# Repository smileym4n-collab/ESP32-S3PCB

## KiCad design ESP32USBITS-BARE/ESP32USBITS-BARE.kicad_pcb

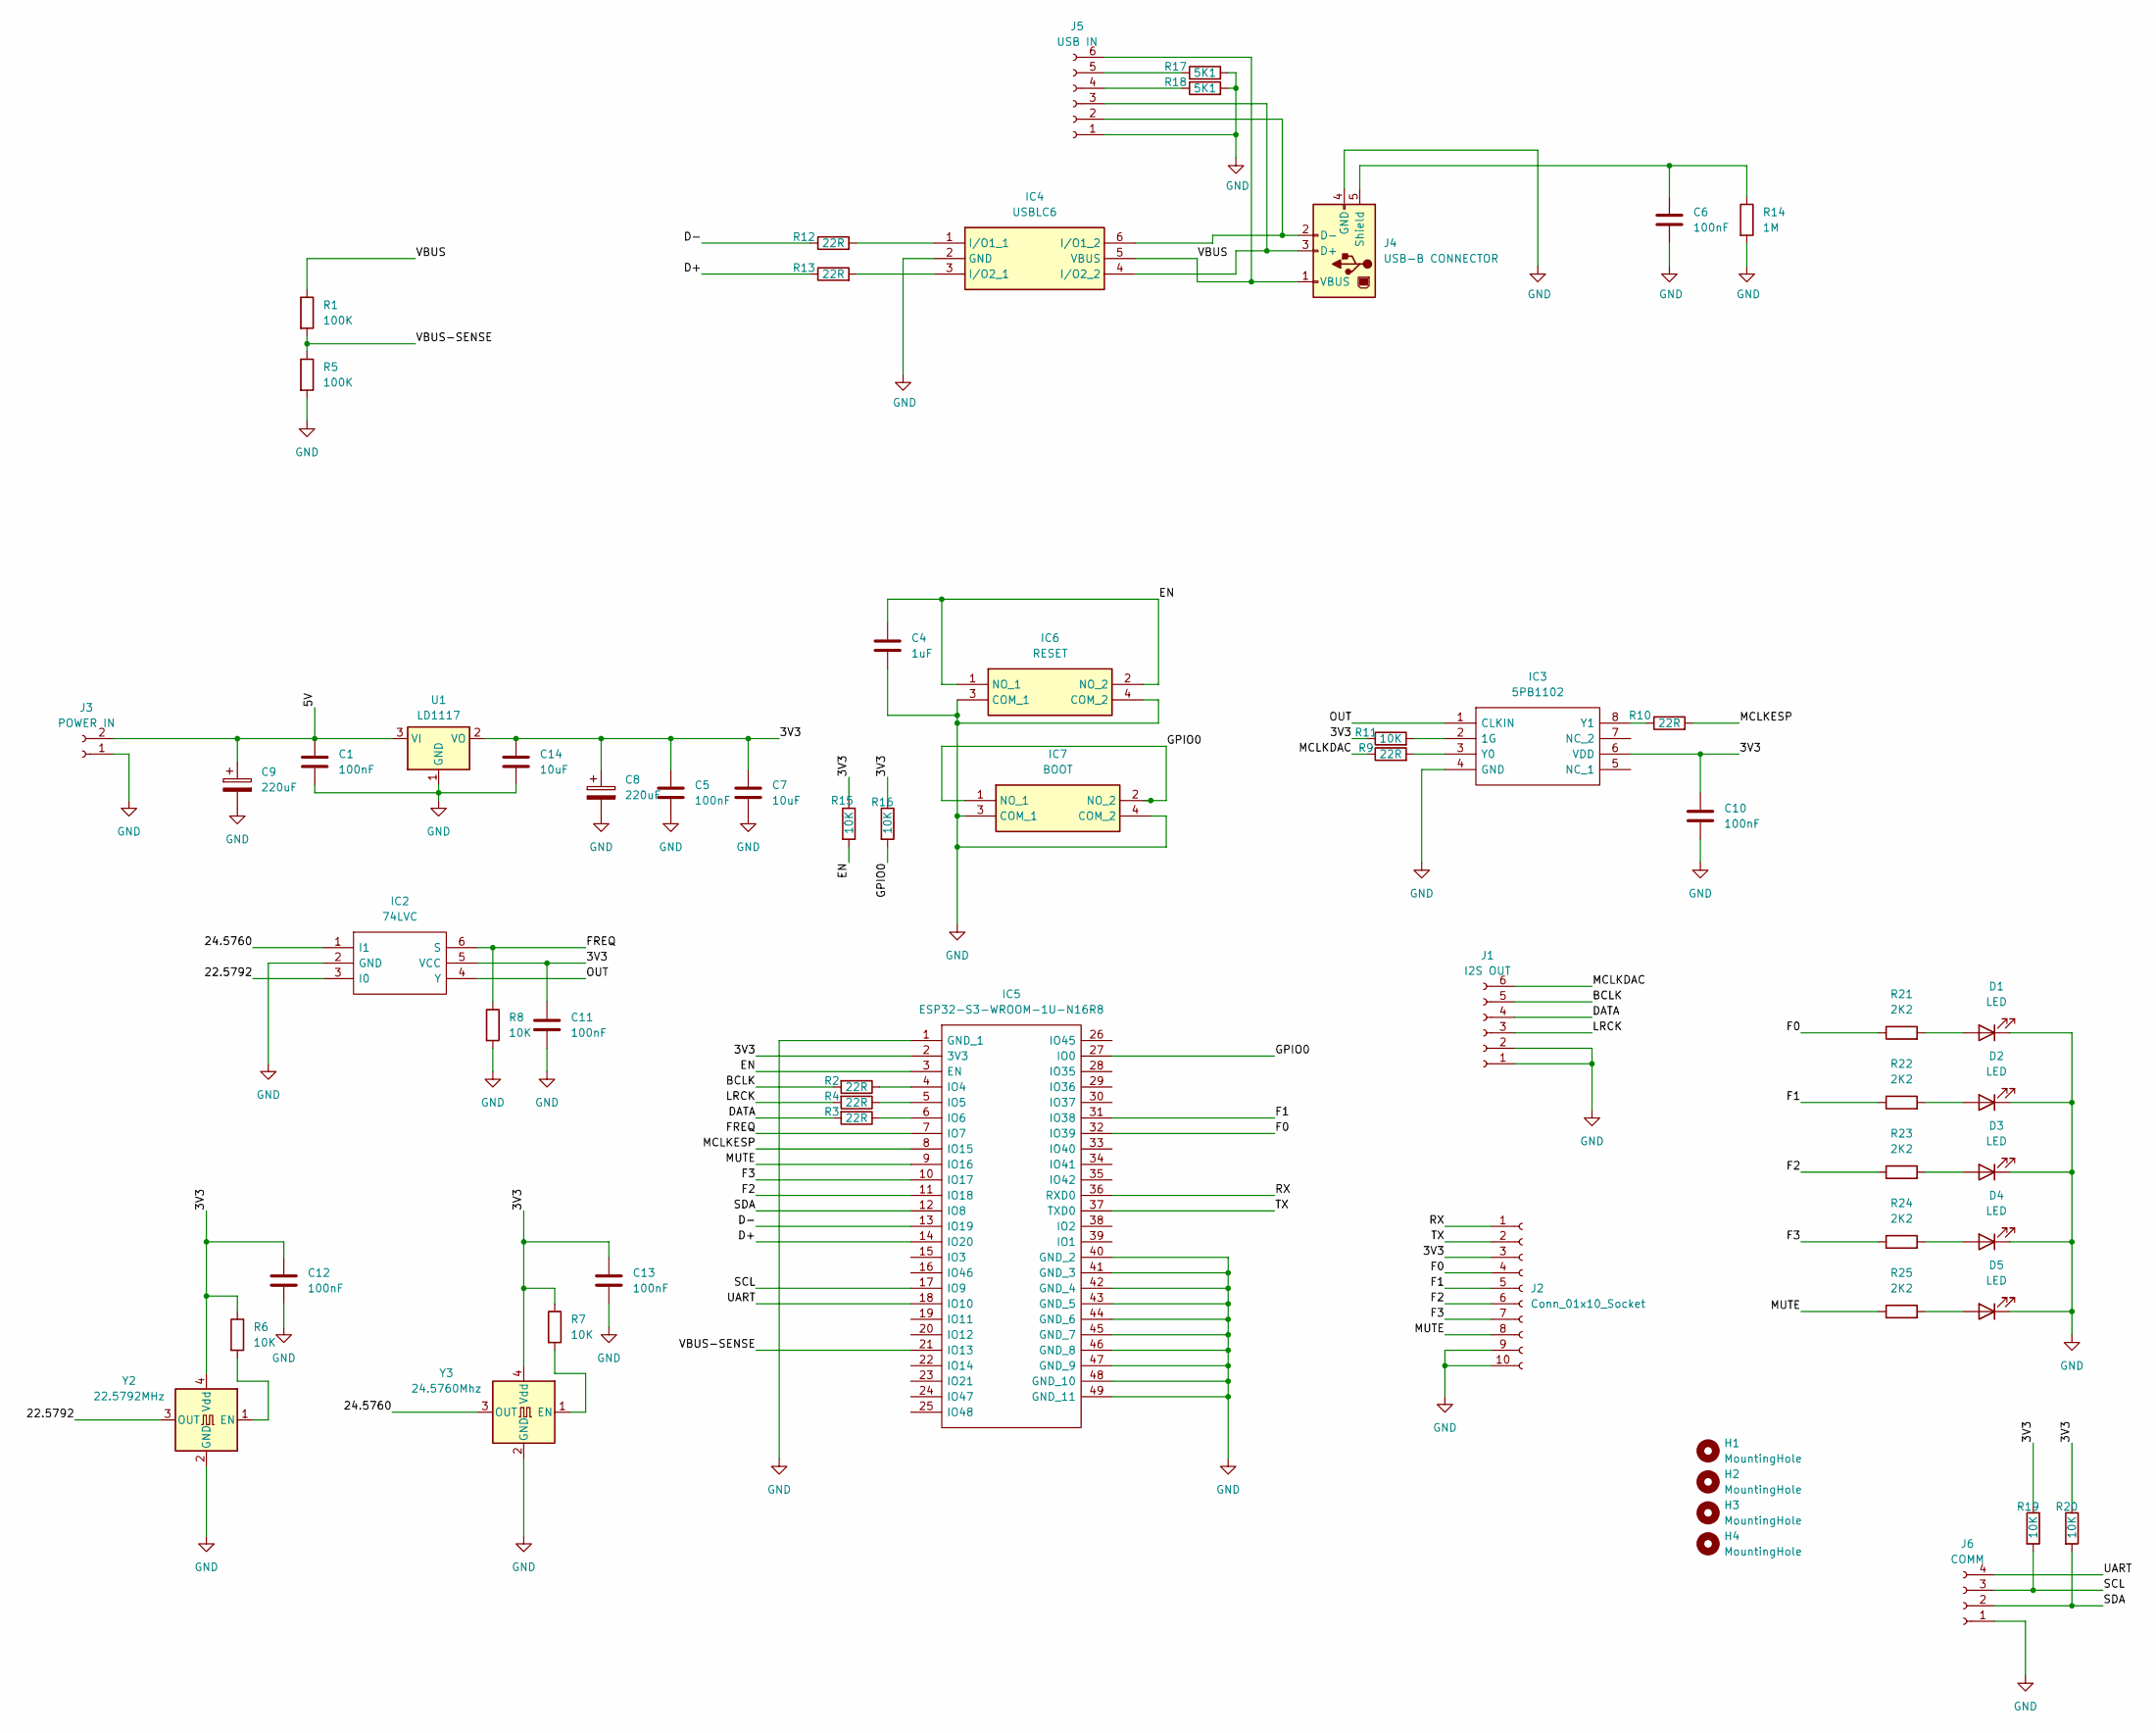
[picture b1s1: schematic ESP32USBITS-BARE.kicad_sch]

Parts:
C1, C5, C6, C10, C11, C12, C13: 100nF; C_1206_3216Metric_Pad1.33x1.80mm_HandSolder
C4: 1uF; C_1206_3216Metric_Pad1.33x1.80mm_HandSolder
C7: 10uF; C_1206_3216Metric_Pad1.33x1.80mm_HandSolder
C8, C9: 220uF; CP_Radial_D6.3mm_P2.50mm
C14: 10uF; C_0805_2012Metric_Pad1.18x1.45mm_HandSolder
D1, D2, D3, D4, D5: LED; LED_0805_2012Metric_Pad1.15x1.40mm_HandSolder
H1, H2, H3, H4: MountingHole; MountingHole_4mm
IC2: 74LVC; 74CBTLV3257PW; Manufacturer_Part_Number 74LVC1G157GW,125
IC3: 5PB1102; 5PB1102PGGK; Manufacturer_Part_Number 5PB1102PGGK
IC4: USBLC6; SOT-23-6_Handsoldering; Mouser Part Number 511-USBLC6-2SC6
IC5: ESP32-S3-WROOM-1U-N16R8; ESP32S3WROOM1UN16R8; Mouser Part Number 356-ESP32S3WM1UN16R8
IC6: RESET; TS026650BK100SCRD; Mouser Part Number 179-TS026650BK100SCR
IC7: BOOT; TS026650BK100SCRD; Mouser Part Number 179-TS026650BK100SCR
J1: I2S OUT; JST_XH_B6B-XH-A_1x06_P2.50mm_Vertical
J2: Conn_01x10_Socket; PinHeader_1x10_P2.54mm_Vertical
J3: POWER IN; JST_XH_B2B-XH-A_1x02_P2.50mm_Vertical
J4: USB-B CONNECTOR; USBC
J5: USB IN; JST_XH_B6B-XH-A_1x06_P2.50mm_Vertical
J6: COMM; PinHeader_1x04_P2.54mm_Vertical
R1, R5: 100K; R_0805_2012Metric_Pad1.20x1.40mm_HandSolder
R2, R3, R4, R9, R10, R12, R13: 22R; R_0805_2012Metric_Pad1.20x1.40mm_HandSolder
R6, R7, R8, R11, R15, R16, R19, R20: 10K; R_0603_1608Metric_Pad0.98x0.95mm_HandSolder
R14: 1M; R_0805_2012Metric_Pad1.20x1.40mm_HandSolder
R17, R18: 5K1; R_0805_2012Metric_Pad1.20x1.40mm_HandSolder
R21, R22, R23, R24, R25: 2K2; R_0603_1608Metric_Pad0.98x0.95mm_HandSolder
U1: LD1117; SOT-223-3_TabPin2
Y2: 22.5792MHz; Oscillator_SMD_Abracon_ASE-4Pin_3.2x2.5mm
Y3: 24.5760Mhz; Oscillator_SMD_Abracon_ASE-4Pin_3.2x2.5mm

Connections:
/3V3: C5.1, C7.1, C8.1, C10.1, C11.1, C12.1, C13.1, C14.1, IC2.5 (VCC), IC3.6 (VDD), IC5.2 (3V3), J2.3, R6.1, R7.1, R11.1, R15.1, R16.1, R19.1, R20.1, U1.2 (VO), Y2.4 (Vdd), Y3.4 (Vdd)
/5V: C1.1, C9.1, J3.2, U1.3 (VI)
/22.5792: IC2.3 (I0), Y2.3 (OUT)
/24.5760: IC2.1 (I1), Y3.3 (OUT)
/BCLK: J1.5, R2.2
/D+: IC5.14 (IO20), R13.1
/D-: IC5.13 (IO19), R12.1
/DATA: J1.4, R3.2
/EN: C4.1, IC5.3 (EN), IC6.1 (NO_1), IC6.2 (NO_2), R15.2
/F0: IC5.32 (IO39), J2.4, R21.1
/F1: IC5.31 (IO38), J2.5, R22.1
/F2: IC5.11 (IO18), J2.6, R23.1
/F3: IC5.10 (IO17), J2.7, R24.1
/FREQ: IC2.6 (S), IC5.7 (IO7), R8.1
/GPIO0: IC5.27 (IO0), IC7.1 (NO_1), IC7.2 (NO_2), R16.2
/LRCK: J1.3, R4.2
/MCLKDAC: J1.6, R9.1
/MCLKESP: IC5.8 (IO15), R10.2
/MUTE: IC5.9 (IO16), J2.8, R25.1
/OUT: IC2.4 (Y), IC3.1 (CLKIN)
/RX: IC5.36 (RXD0), J2.1
/SCL: IC5.17 (IO9), J6.3, R19.2
/SDA: IC5.12 (IO8), J6.2, R20.2
/TX: IC5.37 (TXD0), J2.2
/UART: IC5.18 (IO10), J6.4
/VBUS: IC4.5 (VBUS), J4.1 (VBUS), J5.6, R1.1
/VBUS-SENSE: IC5.21 (IO13), R1.2, R5.1
GND: C1.2, C4.2, C5.2, C6.2, C7.2, C8.2, C9.2, C10.2, C11.2, C12.2, C13.2, C14.2, D1.1 (K), D2.1 (K), D3.1 (K), D4.1 (K), D5.1 (K), IC2.2 (GND), IC3.4 (GND), IC4.2 (GND), IC5.1 (GND_1), IC5.40 (GND_2), IC5.41 (GND_3), IC5.42 (GND_4), IC5.43 (GND_5), IC5.44 (GND_6), IC5.45 (GND_7), IC5.46 (GND_8), IC5.47 (GND_9), IC5.48 (GND_10), IC5.49 (GND_11), IC6.3 (COM_1), IC6.4 (COM_2), IC7.3 (COM_1), IC7.4 (COM_2), J1.1, J1.2, J2.9, J2.10, J3.1, J4.4 (GND), J5.1, J6.1, R5.2, R8.2, R14.2, R17.2, R18.2, U1.1 (GND), Y2.2 (GND), Y3.2 (GND)
unnamed: D1.2 (A), R21.2
unnamed: D2.2 (A), R22.2
unnamed: D3.2 (A), R23.2
unnamed: D4.2 (A), R24.2
unnamed: D5.2 (A), R25.2
unnamed: IC3.2 (1G), R11.2
unnamed: IC3.3 (Y0), R9.2
unnamed: IC3.8 (Y1), R10.1
unnamed: IC4.1 (I/O1_1), R12.2
unnamed: IC4.6 (I/O1_2), J4.2 (D-), J5.2
unnamed: IC4.3 (I/O2_1), R13.2
unnamed: IC4.4 (I/O2_2), J4.3 (D+), J5.3
unnamed: IC5.4 (IO4), R2.1
unnamed: IC5.5 (IO5), R4.1
unnamed: IC5.6 (IO6), R3.1
unnamed: C6.1, J4.5 (Shield), R14.1
unnamed: J5.4, R18.1
unnamed: J5.5, R17.1
unnamed: R6.2, Y2.1 (EN)
unnamed: R7.2, Y3.1 (EN)

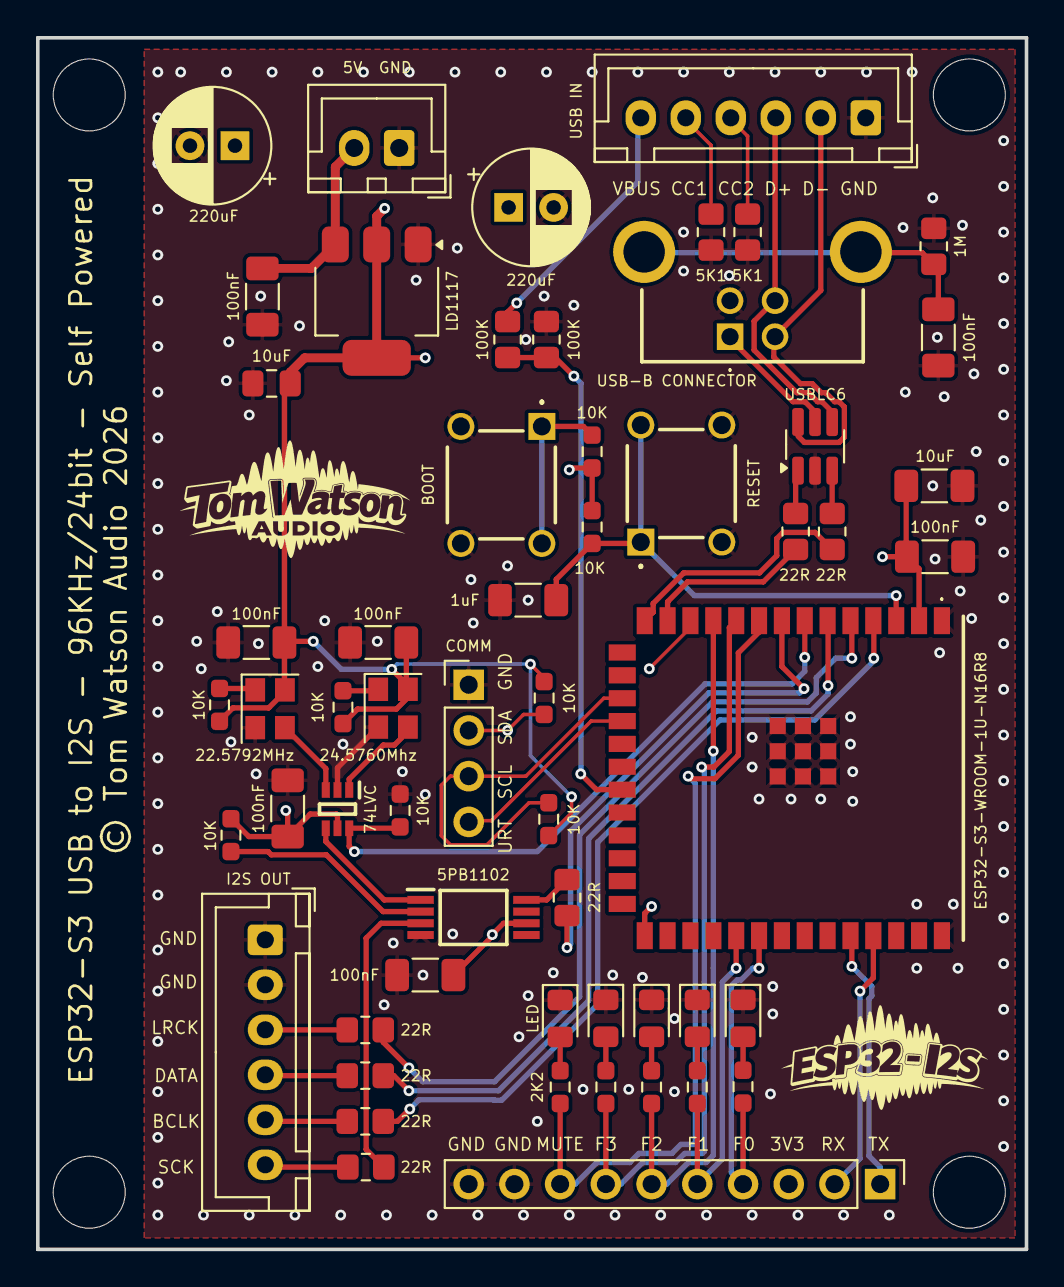
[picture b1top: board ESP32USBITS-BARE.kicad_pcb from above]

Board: 4 copper layers, 54.9 x 67.3 mm, 61 parts (0 on the bottom side), 48 nets.

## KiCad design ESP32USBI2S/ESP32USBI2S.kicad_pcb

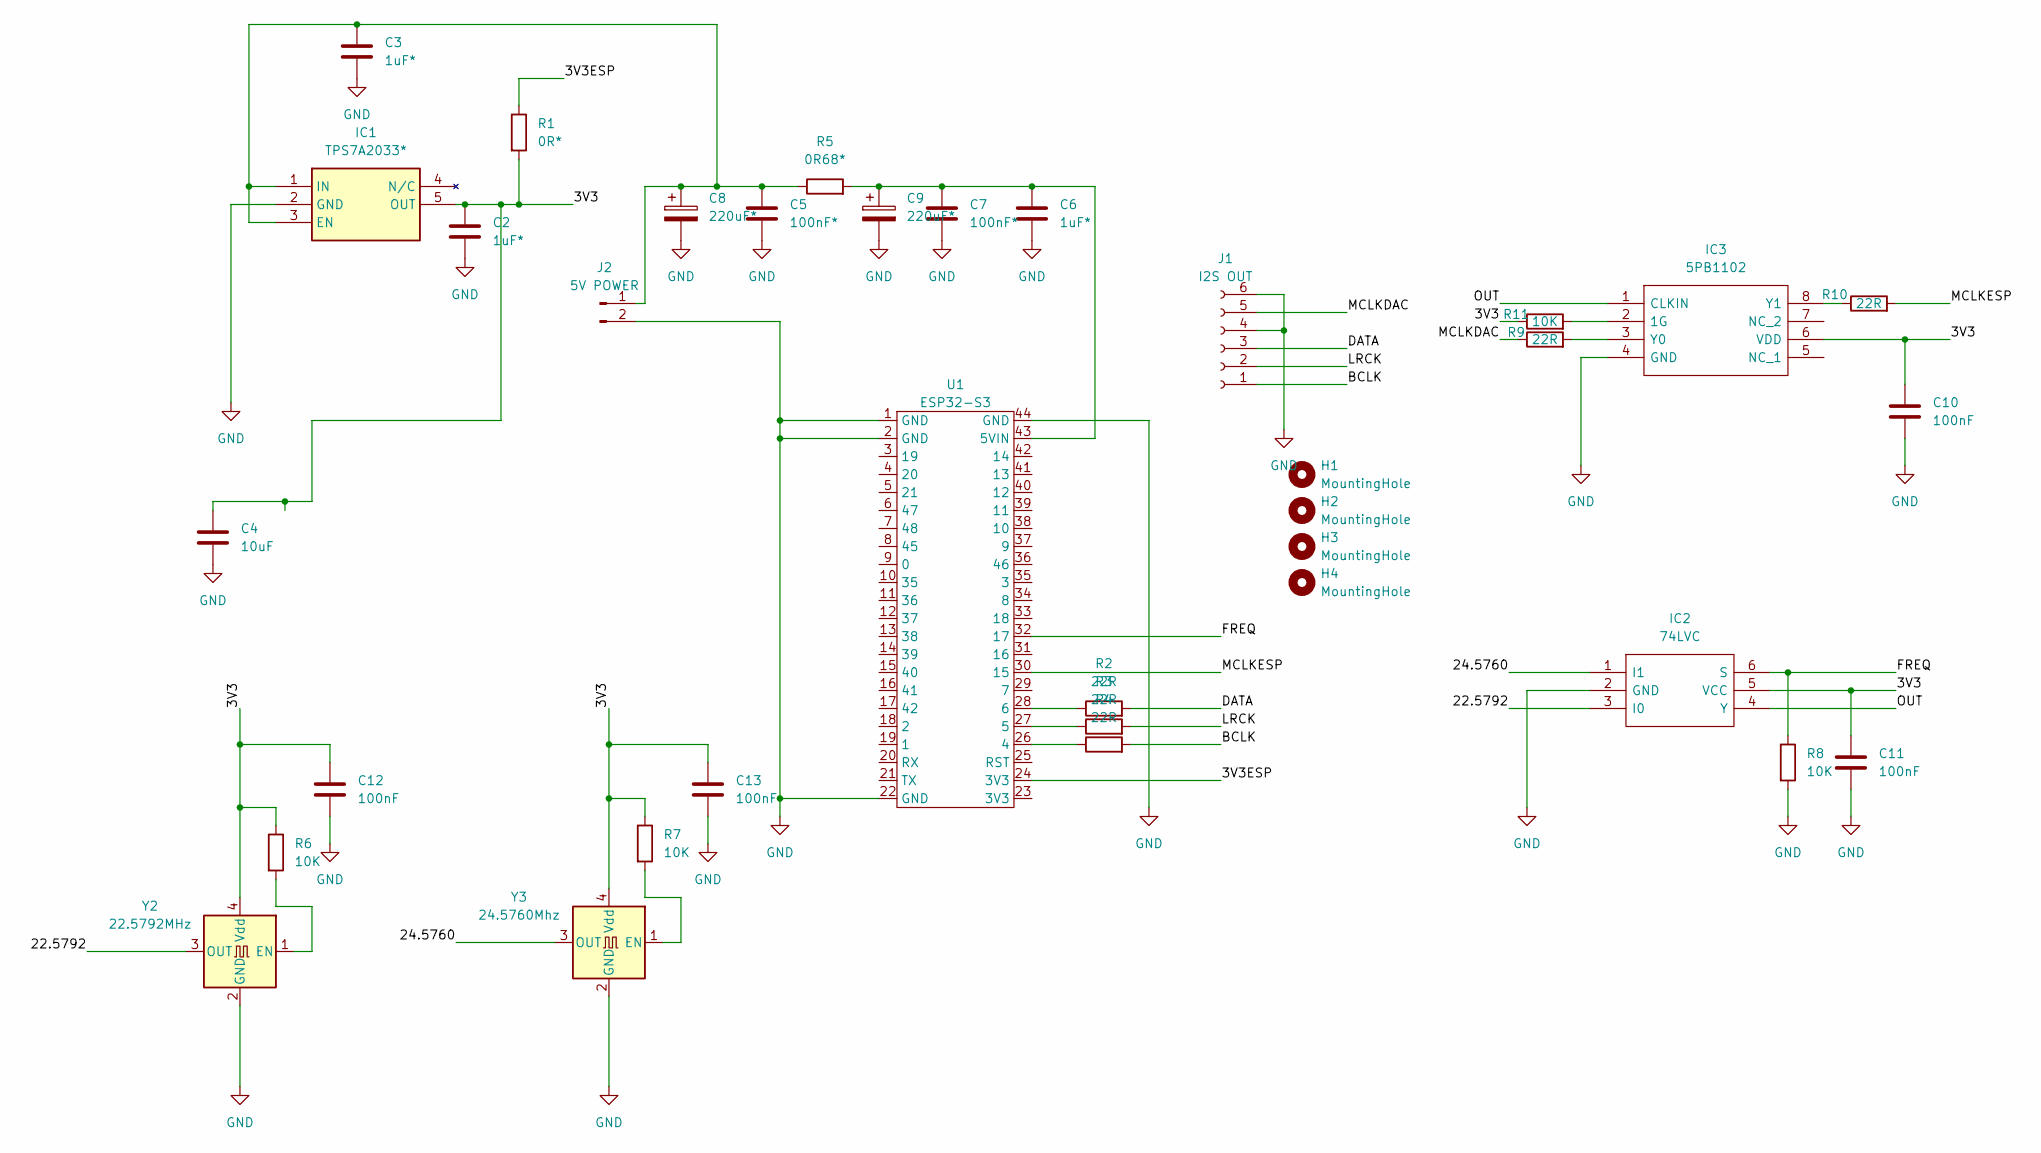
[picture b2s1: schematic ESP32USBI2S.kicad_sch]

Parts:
C2, C3, C6: 1uF*; C_1206_3216Metric_Pad1.33x1.80mm_HandSolder
C4: 10uF; C_1206_3216Metric_Pad1.33x1.80mm_HandSolder
C5, C7: 100nF*; C_1206_3216Metric_Pad1.33x1.80mm_HandSolder
C8, C9: 220uF*; CP_Radial_D6.3mm_P2.50mm
C10, C11, C12, C13: 100nF; C_1206_3216Metric_Pad1.33x1.80mm_HandSolder
H1, H2, H3, H4: MountingHole; MountingHole_4mm
IC1: TPS7A2033*; SOT95P280X145-5N; Mouser Part Number 595-TPS7A2033PDBVR
IC2: 74LVC; 74CBTLV3257PW; Manufacturer_Part_Number 74LVC1G157GW,125
IC3: 5PB1102; 5PB1102PGGK; Manufacturer_Part_Number 5PB1102PGGK
J1: I2S OUT; Molex_KK-254_AE-6410-06A_1x06_P2.54mm_Vertical
J2: 5V POWER; JST_XH_B2B-XH-A_1x02_P2.50mm_Vertical
R1: 0R*; R_0805_2012Metric_Pad1.20x1.40mm_HandSolder
R2, R3, R4, R9, R10: 22R; R_0603_1608Metric_Pad0.98x0.95mm_HandSolder
R5: 0R68*; R_1206_3216Metric_Pad1.30x1.75mm_HandSolder
R6, R7, R8, R11: 10K; R_0603_1608Metric_Pad0.98x0.95mm_HandSolder
U1: ESP32-S3; ESP32S3
Y2: 22.5792MHz; Oscillator_SMD_Abracon_ASE-4Pin_3.2x2.5mm
Y3: 24.5760Mhz; Oscillator_SMD_Abracon_ASE-4Pin_3.2x2.5mm

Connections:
/3V3: C2.1, C4.1, C10.1, C11.1, C12.1, C13.1, IC1.5 (OUT), IC2.5 (VCC), IC3.6 (VDD), R1.2, R6.1, R7.1, R11.1, Y2.4 (Vdd), Y3.4 (Vdd)
/3V3ESP: R1.1, U1.24 (3V3)
/22.5792: IC2.3 (I0), Y2.3 (OUT)
/24.5760: IC2.1 (I1), Y3.3 (OUT)
/BCLK: J1.1, R4.2
/DATA: J1.3, R2.2
/FREQ: IC2.6 (S), R8.1, U1.32 (17)
/LRCK: J1.2, R3.2
/MCLKDAC: J1.5, R9.1
/MCLKESP: R10.2, U1.30 (15)
/OUT: IC2.4 (Y), IC3.1 (CLKIN)
GND: C2.2, C3.2, C4.2, C5.2, C6.2, C7.2, C8.2, C9.2, C10.2, C11.2, C12.2, C13.2, IC1.2 (GND), IC2.2 (GND), IC3.4 (GND), J1.4, J1.6, J2.2, R8.2, U1.1 (GND), U1.2 (GND), U1.22 (GND), U1.44 (GND), Y2.2 (GND), Y3.2 (GND)
unnamed: C3.1, C5.1, C8.1, IC1.1 (IN), IC1.3 (EN), J2.1, R5.1
unnamed: IC3.2 (1G), R11.2
unnamed: IC3.3 (Y0), R9.2
unnamed: IC3.8 (Y1), R10.1
unnamed: R4.1, U1.26 (4)
unnamed: R3.1, U1.27 (5)
unnamed: C6.1, C7.1, C9.1, R5.2, U1.43 (5VIN)
unnamed: R2.1, U1.28 (6)
unnamed: R6.2, Y2.1 (EN)
unnamed: R7.2, Y3.1 (EN)

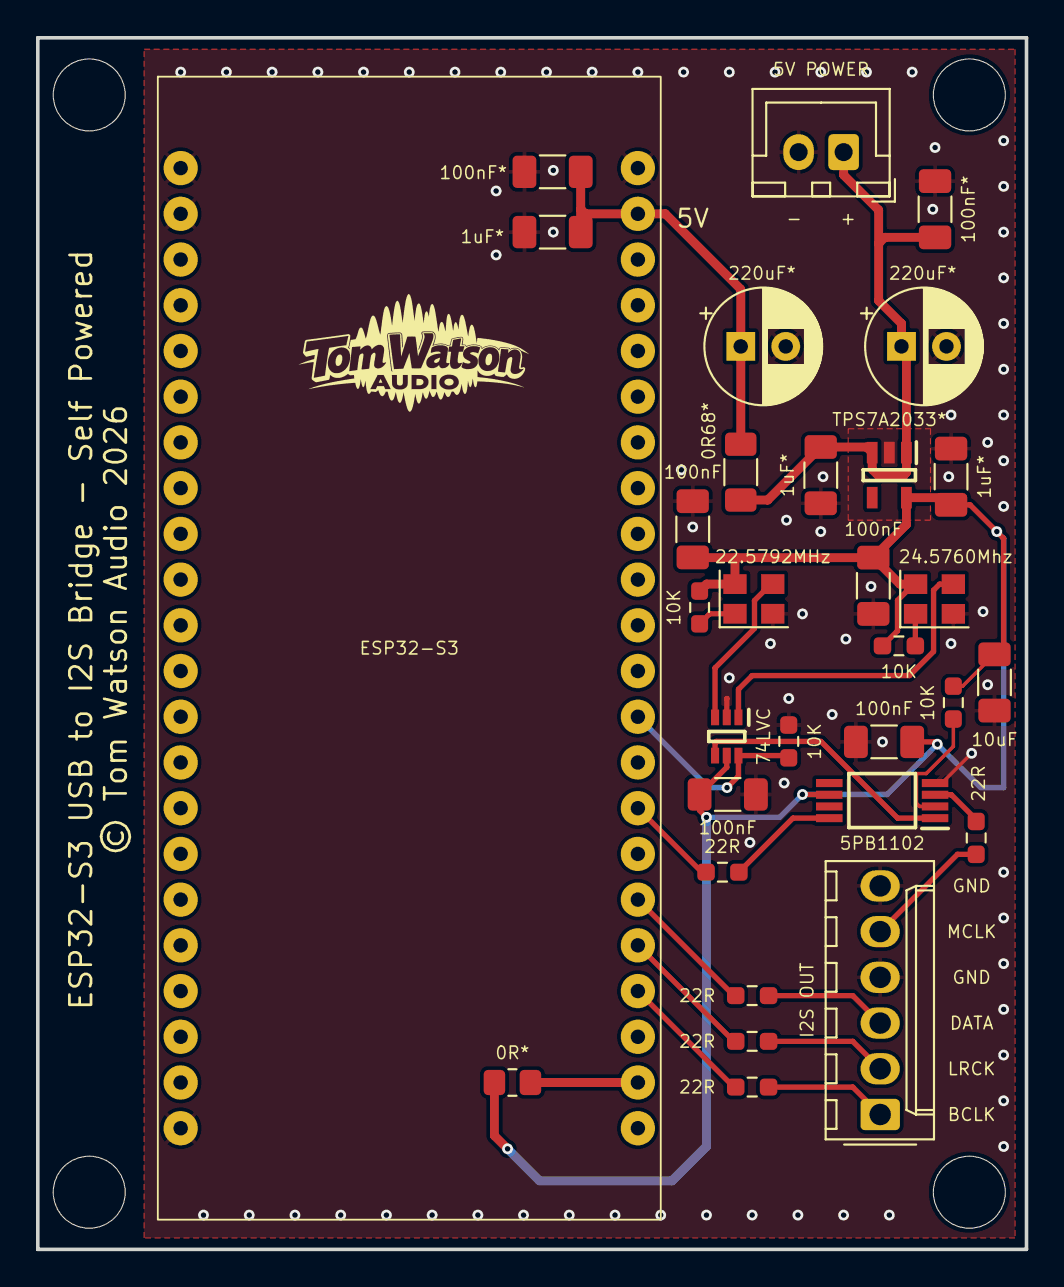
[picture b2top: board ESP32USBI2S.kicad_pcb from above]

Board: 2 copper layers, 54.9 x 67.3 mm, 35 parts (0 on the bottom side), 22 nets.

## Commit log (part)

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2026-06-04 final design
2026-06-09 design for bare module
2026-06-12 more work

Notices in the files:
ESP32USBI2S/ESP32USBI2S.kicad_pcb:
© Tom Watson Audio 2026
